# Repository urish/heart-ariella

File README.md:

# Heart-shaped Flashlight for Ariella

## Links

[A Practical Guide to Designing PCB Art](https://medium.com/@urish/a-practical-guide-to-designing-pcb-art-b5aa22926a5c) - A blog post explaining how I designed and manufactured the board

The project files are available either in [KiCad](kicad_leds/) or [Eagle](eagle/) format. The boards were manufactured by [OSH Park](https://oshpark.com).

## License

[CC-BY-SA](https://creativecommons.org/licenses/by-sa/4.0/)

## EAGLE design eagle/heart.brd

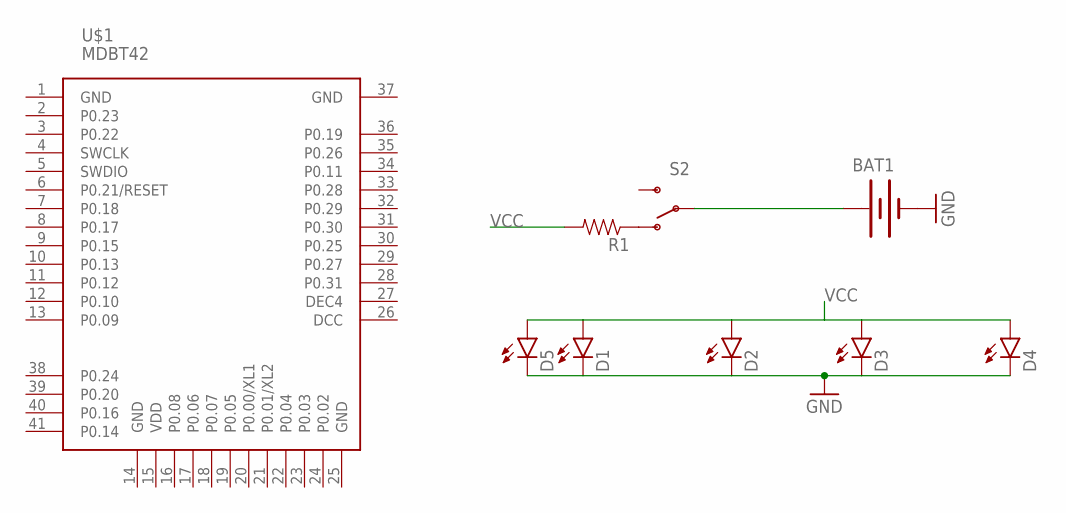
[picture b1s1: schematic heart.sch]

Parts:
BAT1: BATTERY12MM; BATTCON_12MM
D1, D2, D3, D4, D5: LED0603; LED-0603
R1: RESISTOR0603; 0603-RES
S2: SWITCH-SPDTSMD_NOHOLE; AYZ0202_NOHOLE
U$1: MDBT42

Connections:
GND: BAT1.GND (-), D1.C, D2.C, D3.C, D4.C, D5.C
unnamed: BAT1.PWR@1 (+), S2.2
unnamed: R1.1, S2.1 (O)
VCC: D1.A, D2.A, D3.A, D4.A, D5.A, R1.2

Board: 2 copper layers, 9 parts (5 on the bottom side), 4 nets, no tracks yet.

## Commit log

2017-03-21 add heart photos
2017-08-18 move eagle files to `eagle` dir
2017-08-18 add heart shape SVG
2017-08-18 add kicad art files
2017-08-19 slightly modify inner heart shape
2017-08-19 set PCB gerber plot settings
2017-08-19 Restore original eagle files
2017-08-24 add kicad pcb with electronics
    5 leds + switch + battery holder
2017-09-02 Add links to README

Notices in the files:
parts and their libraries:
SparkFun-LED: Licensing: Creative Commons ShareAlike 4.0 International - https://creativecommons.org/licenses/by-sa/4.0
